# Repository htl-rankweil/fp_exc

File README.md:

# `EXC` - EXtendable Controller (Erweiterbarer Mikrocontroller)

The `EXC` is a microcontroller board with an [ATmega16A](#additional-information)/[ATmega164A](#additional-information). The Board can be powerd over USB or from an external Source (`9-15V`) and used with common Voltages of `3V3` or `5V`. Over the USB port it is also possible to establish a serial (`uart`) connection to a computer. The Board itself offers a `SPI`, `I2C` interface for bus systems, a interface for connection to external interrupts of the microcontroller and a analog interface for reading analog data into the microcontroller. At `DP1` a [Display](#additional-information) can be connected to the board. The available demo firmware offers a quick demonstartion of the board functionallity. Check the [Software](#software) section to get more information.

| Experience | Level |
|:------------|:-----:|
| Soldering   |  |
| Software    |  |

# Downloads

| Type      | File               | Description              |
|:---------:|:------------------:|:-------------------------|
| Schematic | [pdf](https://github.com/0x007E/exc/releases/latest/download/schematic.pdf) / [cadlab](https://cadlab.io/project/28573/main/files) | Schematic files |
| Board | [pdf](https://github.com/0x007E/exc/releases/latest/download/pcb.pdf) / [cadlab](https://cadlab.io/project/28573/main/files) | Board file |
| Drill | [pdf](https://github.com/0x007E/exc/releases/latest/download/drill.pdf) | Drill file |
| Gerber | [zip](https://github.com/0x007E/exc/releases/latest/download/kicad.zip) / [tar](https://github.com/0x007E/exc/releases/latest/download/kicad.tar.gz) | Gerber/Drill files |
| Firmware | [zip](https://github.com/0x007E/exc/releases/latest/download/firmware.zip) / [tar](https://github.com/0x007E/exc/releases/latest/download/firmware.tar.gz) | Firmware for ATmega164A |

# Hardware

The pcb is created with `KiCAD`. All files are built with `github actions` so that they are ready for a production environment.

## PCB

The circuit board is populated on one side. The best way for soldering is within a vapor phase soldering system.

### Top Layer

### Bottom Layer

# Configuration

With Jumper `J13` the `EXC` system is getting bus powered (`5V`). If the system runs with `5V` jumper `J12` has to be shorten between `2-3`. When the system is driven by an external source through the step-down converter the system voltage is switchable between `5V` and `3V3` over the slider switch `SW6`. If `3V3` are choosen the jumper `J12` should be shorten between `1-2`.

> Only change the state of `SW6` with disconnected power source. Also check if jumper `J12` is set correctly!

## LEDs/I2C

To enable the LEDs `LED0-1` jumper `J10` has to be shorten. If the `I2C` interface should be used the jumper `J10` has to be removed.

## UART

The UART of the `ATmega164A` can be coupled with the USB/UART bridge or with the external UART interface at connector `J5`. To set the transmission over USB/UART bridge jumper `J1` and `J2` should be shorten between `1-2`. For the external UART interface jumper `J1` and `J2` should be shorten between `2-3`.

## Display

The display can be powerd constantly over `J99` shorten between `2-3` or controllabe over the microcontroller pin `PA2` and `J99` shorten between `1-2`.

# Programming

The Firmware of the `EXC` can be programmed with [Microchip Studio](#additional-information) over ISP with an [ATMEL ICE](#additional-information) connected to `J9` of the `EXC`. It is necessary to power the board from outside either over USB or the external power supply during programming.

## FUSES

| Register  | Value  |
|:---------:|:------:|
| `HIGH`    | `0xD8` |
| `LOW`     | `0xFF` |

# Software

## Dataflow diagram

## Structogram

# Additional Information

| Type       | Link               | Description              |
|:----------:|:------------------:|:-------------------------|
| Display | [web](https://at.rs-online.com/web/p/lcd-displays-monochrom/5326385) | Display for extendable controller |
| Microchip Studio | [web](https://www.microchip.com/en-us/tools-resources/develop/microchip-studio) | Download Page for Microchip Studio |
| Atmel ICE | [pdf](https://ww1.microchip.com/downloads/en/DeviceDoc/Atmel-ICE_UserGuide.pdf) | Atmel ICE Datasheet |
| ATmega16A | [pdf](https://ww1.microchip.com/downloads/en/devicedoc/atmel-8154-8-bit-avr-atmega16a_datasheet.pdf) | Microchip ATmega16A Datasheet
| ATmega164A | [pdf](https://ww1.microchip.com/downloads/en/devicedoc/atmel-8272-8-bit-avr-microcontroller-atmega164a_pa-324a_pa-644a_pa-1284_p_datasheet.pdf) | Microchip ATmega164A Datasheet |

---

R. GAECHTER

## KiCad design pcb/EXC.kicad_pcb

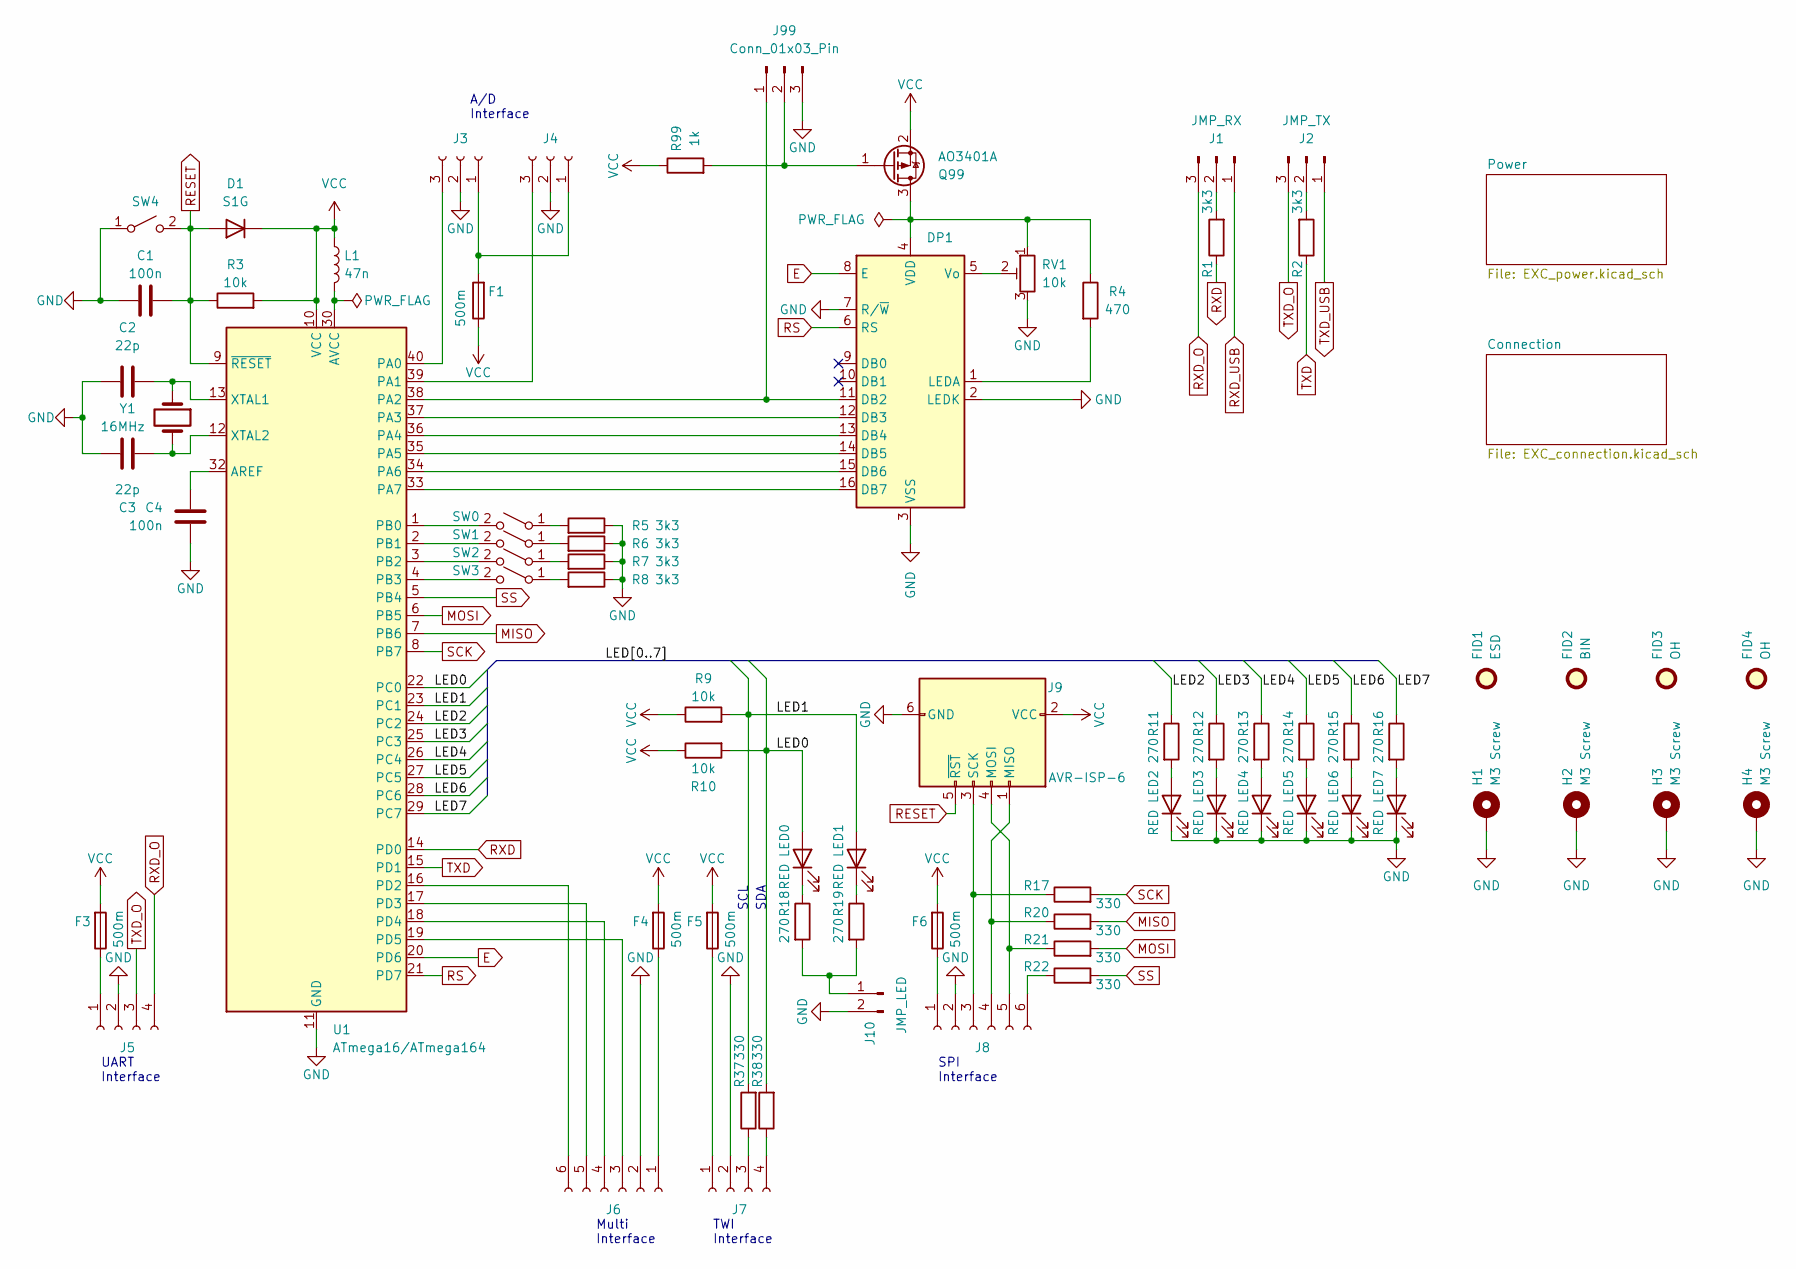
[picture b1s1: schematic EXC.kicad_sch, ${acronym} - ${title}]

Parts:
C1, C4: 100n; C_1206_3216Metric
C2, C3: 22p; C_1206_3216Metric
D1: S1G; D_MiniMELF
DP1: Displaytech_162A_THT
F1, F3, F4, F5, F6: 500m; Fuse_1206_3216Metric
FID1: ESD; ESD-Logo_6.6x6mm_SilkScreen
FID2: BIN; WEEE-Logo_4.2x6mm_SilkScreen
FID3: OH; OSHW-Logo_5.7x6mm_SilkScreen
FID4: OH; QR_0x007e
H1, H2, H3, H4: M3 Screw; MountingHole_3.2mm_M3_DIN965_Pad
J1: JMP_RX; PinHeader_1x03_P2.54mm_Vertical
J2: JMP_TX; PinHeader_1x03_P2.54mm_Vertical
J3, J4: Conn_01x03_Socket; PinSocket_1x03_P2.54mm_Vertical
J5, J7: Conn_01x04_Socket; PinSocket_1x04_P2.54mm_Vertical
J6, J8: Conn_01x06_Socket; PinSocket_1x06_P2.54mm_Vertical
J9: AVR-ISP-6; PinHeader_2x03_P2.54mm_Vertical
J10: JMP_LED; PinHeader_1x02_P2.54mm_Vertical
J99: Conn_01x03_Pin; PinHeader_1x03_P2.54mm_Horizontal
L1: 47n; L_1206_3216Metric_Pad1.42x1.75mm_HandSolder
LED0, LED1, LED2, LED3, LED4, LED5, LED6, LED7: RED; LED_1206_3216Metric
Q99: AO3401A; SOT-23
R1, R2, R5, R6, R7, R8: 3k3; R_1206_3216Metric
R3, R9, R10: 10k; R_1206_3216Metric
R4: 470; R_1206_3216Metric
R11, R12, R13, R14, R15, R16, R18, R19: 270; R_1206_3216Metric
R17, R20, R21, R22, R37, R38: 330; R_1206_3216Metric
R99: 1k; R_1206_3216Metric
RV1: 10k; Potentiometer_Bourns_3266W_Vertical
SW0, SW1, SW2, SW3, SW4: SW_SPST; SW_SPST_PTS645
U1: ATmega16/ATmega164; DIP-40_W15.24mm_LongPads
Y1: 16MHz; Crystal_SMD_Abracon_ABM3-2Pin_5.0x3.2mm

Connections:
/LED0: LED0.2 (A), R10.2, R38.2, U1.22 (PC0)
/LED1: LED1.2 (A), R9.2, R37.2, U1.23 (PC1)
/LED2: R11.1, U1.24 (PC2)
/LED3: R12.1, U1.25 (PC3)
/LED4: R13.1, U1.26 (PC4)
/LED5: R14.1, U1.27 (PC5)
/LED6: R15.1, U1.28 (PC6)
/LED7: R16.1, U1.29 (PC7)
E: DP1.8 (E), U1.20 (PD6)
GND: C1.1, C2.1, C3.1, C4.2, DP1.2 (LEDK), DP1.3 (VSS), DP1.7 (R/~W), H1.1, H2.1, H3.1, H4.1, J3.2, J4.2, J5.2, J6.2, J7.2, J8.2, J9.6 (GND), J10.2, J99.3, LED2.1 (K), LED3.1 (K), LED4.1 (K), LED5.1 (K), LED6.1 (K), LED7.1 (K), R5.1, R6.1, R7.1, R8.1, RV1.3, SW4.1 (A), U1.11 (GND), U1.31 (GND); also elsewhere on the board
MISO: R20.2, U1.7 (PB6)
MOSI: R21.2, U1.6 (PB5)
unnamed: DP1.11 (DB2), J99.1, U1.38 (PA2)
unnamed: DP1.12 (DB3), U1.37 (PA3)
unnamed: DP1.13 (DB4), U1.36 (PA4)
unnamed: DP1.14 (DB5), U1.35 (PA5)
unnamed: DP1.15 (DB6), U1.34 (PA6)
unnamed: DP1.16 (DB7), U1.33 (PA7)
unnamed: DP1.1 (LEDA), R4.2
unnamed: DP1.4 (VDD), Q99.3 (D), R4.1, RV1.1
unnamed: DP1.5 (Vo), RV1.2
unnamed: J1.2, R1.2
unnamed: J2.2, R2.2
unnamed: F1.2, J3.1, J4.1
unnamed: J3.3, U1.40 (PA0)
unnamed: J4.3, U1.39 (PA1)
unnamed: F3.1, J5.1
unnamed: F4.1, J6.1
unnamed: J6.3, U1.19 (PD5)
unnamed: J6.4, U1.18 (PD4)
unnamed: J6.5, U1.17 (PD3)
unnamed: J6.6, U1.16 (PD2)
unnamed: F5.1, J7.1
unnamed: J7.3, R37.1
unnamed: J7.4, R38.1
unnamed: F6.1, J8.1
unnamed: J8.3, J9.3 (SCK), R17.1
unnamed: J8.4, J9.1 (MISO), R20.1
unnamed: J8.5, J9.4 (MOSI), R21.1
unnamed: J8.6, R22.1
unnamed: J10.1, R18.2, R19.2
unnamed: J99.2, Q99.1 (G), R99.2
unnamed: LED0.1 (K), R18.1
unnamed: LED1.1 (K), R19.1
unnamed: LED2.2 (A), R11.2
unnamed: LED3.2 (A), R12.2
unnamed: LED4.2 (A), R13.2
unnamed: LED5.2 (A), R14.2
unnamed: LED6.2 (A), R15.2
unnamed: LED7.2 (A), R16.2
unnamed: R5.2, SW0.1 (A)
unnamed: SW0.2 (B), U1.1 (PB0)
unnamed: R6.2, SW1.1 (A)
unnamed: SW1.2 (B), U1.2 (PB1)
unnamed: R7.2, SW2.1 (A)
unnamed: SW2.2 (B), U1.3 (PB2)
unnamed: R8.2, SW3.1 (A)
unnamed: SW3.2 (B), U1.4 (PB3)
unnamed: C4.1, U1.32 (AREF)
unnamed: L1.2, U1.30 (AVCC)
unnamed: C2.2, U1.13 (XTAL1), Y1.1
unnamed: C3.2, U1.12 (XTAL2), Y1.2
RESET: C1.2, D1.2 (A), J9.5 (~RST), R3.1, SW4.2 (B), U1.9 (~RESET)
RS: DP1.6 (RS), U1.21 (PD7)
RXD: R1.1, U1.14 (PD0)
RXD_O: J1.3, J5.4
RXD_USB: J1.1; also elsewhere on the board
SCK: R17.2, U1.8 (PB7)
SS: R22.2, U1.5 (PB4)
TXD: R2.1, U1.15 (PD1)
TXD_O: J2.3, J5.3
TXD_USB: J2.1; also elsewhere on the board
VCC: D1.1 (K), F1.1, F3.2, F4.2, F5.2, F6.2, J9.2 (VCC), L1.1, Q99.2 (S), R3.2, R9.1, R10.1, R99.1, U1.10 (VCC); also elsewhere on the board

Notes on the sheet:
Multi Interface
UART Interface
A/D Interface
TWI Interface
SCL
SDA
SPI Interface

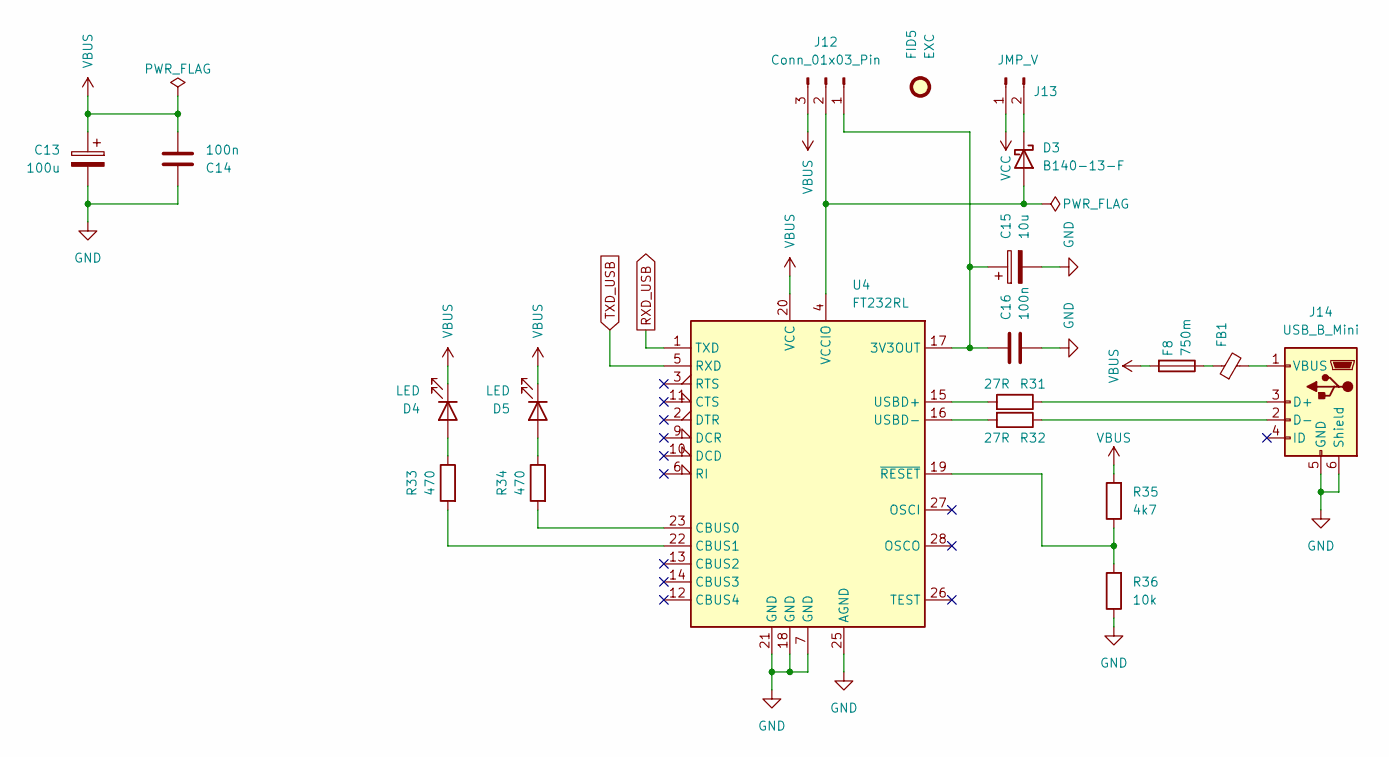
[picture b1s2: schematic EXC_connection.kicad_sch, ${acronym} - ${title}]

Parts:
C13: 100u; CP_Elec_5x5.4
C14, C16: 100n; C_1206_3216Metric
C15: 10u; CP_Elec_5x5.4
D3: B140-13-F; D_SMA
D4, D5: LED; LED_1206_3216Metric
F8: 750m; Fuse_1206_3216Metric
FB1: FerriteBead_Small; L_1206_3216Metric
FID5: EXC; Symbol_Attention_2x2mm_SilkScreen
J12: Conn_01x03_Pin; PinHeader_1x03_P2.54mm_Vertical
J13: JMP_V; PinHeader_1x02_P2.54mm_Vertical
J14: USB_B_Mini; USB_Mini-B_Lumberg_2486_01_Horizontal
R31, R32: 27R; R_1206_3216Metric
R33, R34: 470; R_1206_3216Metric
R35: 4k7; R_1206_3216Metric
R36: 10k; R_1206_3216Metric
U4: FT232RL; SSOP-28_5.3x10.2mm_P0.65mm

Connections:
GND: C13.2, C14.2, C15.2, C16.1, J14.5 (GND), J14.6 (Shield), R36.1, U4.7 (GND), U4.18 (GND), U4.21 (GND), U4.25 (AGND); also elsewhere on the board
unnamed: D3.2 (A), J12.2, U4.4 (VCCIO)
unnamed: D3.1 (K), J13.2
unnamed: D4.2 (A), R33.1
unnamed: D5.2 (A), R34.1
unnamed: F8.1, FB1.1
unnamed: C15.1, C16.2, J12.1, U4.17 (3V3OUT)
unnamed: J14.3 (D+), R31.1
unnamed: J14.2 (D-), R32.1
unnamed: FB1.2, J14.1 (VBUS)
unnamed: R34.2, U4.23 (CBUS0)
unnamed: R33.2, U4.22 (CBUS1)
unnamed: R31.2, U4.15 (USBD+)
unnamed: R32.2, U4.16 (USBD-)
unnamed: R35.1, R36.2, U4.19 (~RESET)
RXD_USB: U4.1 (TXD); also elsewhere on the board
TXD_USB: U4.5 (RXD); also elsewhere on the board
VBUS: C13.1, C14.1, D4.1 (K), D5.1 (K), F8.2, J12.3, R35.2, U4.20 (VCC)
VCC: J13.1; also elsewhere on the board

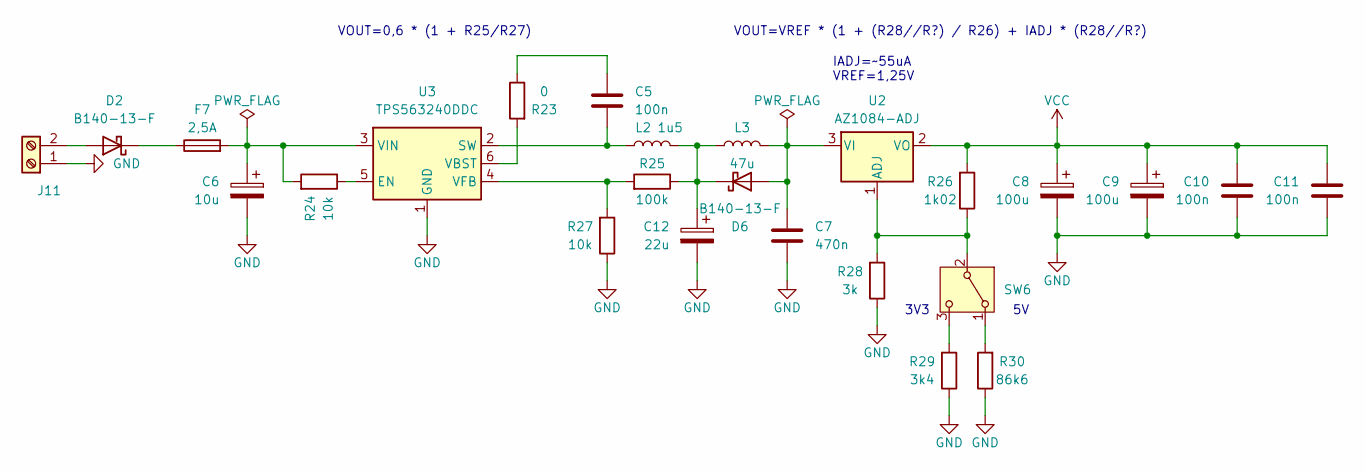
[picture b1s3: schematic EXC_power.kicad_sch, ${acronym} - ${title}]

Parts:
C5, C10, C11: 100n; C_1206_3216Metric
C6: 10u; CP_Elec_5x5.4
C7: 470n; C_1206_3216Metric
C8, C9: 100u; CP_Elec_5x5.4
C12: 22u; CP_Elec_5x5.4
D2, D6: B140-13-F; D_SMA
F7: 2,5A; Fuse_1812_4532Metric
J11: Screw_Terminal_01x02; TerminalBlock_RND_205-00001_1x02_P5.00mm_Horizontal
L2: 1u5; L_Bourns_SRP7028A_7.3x6.6mm
L3: 47u; L_Bourns_SRN8040TA
R23: 0; R_1206_3216Metric
R24, R27: 10k; R_1206_3216Metric
R25: 100k; R_1206_3216Metric
R26: 1k02; R_1206_3216Metric
R28: 3k; R_1206_3216Metric
R29: 3k4; R_1206_3216Metric
R30: 86k6; R_1206_3216Metric
SW6: SW_SPDT; SW_SPDT_CK_JS102011SAQN
U2: AZ1084-ADJ; TO-263-2
U3: TPS563240DDC; SOT-23-6

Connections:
GND: C6.2, C7.1, C8.2, C9.2, C10.1, C11.1, C12.2, J11.1, R27.1, R28.1, R29.1, R30.1, U3.1 (GND); also elsewhere on the board
unnamed: C5.2, R23.1
unnamed: D2.2 (A), J11.2
unnamed: D2.1 (K), F7.1
unnamed: C7.2, D6.2 (A), L3.2, U2.3 (VI)
unnamed: C12.1, D6.1 (K), L2.2, L3.1, R25.1
unnamed: R30.2, SW6.1 (A)
unnamed: R26.1, R28.2, SW6.2 (B), U2.1 (ADJ)
unnamed: R29.2, SW6.3 (C)
unnamed: R24.1, U3.5 (EN)
unnamed: C5.1, L2.1, U3.2 (SW)
unnamed: R23.2, U3.6 (VBST)
unnamed: R25.2, R27.2, U3.4 (VFB)
unnamed: C6.1, F7.2, R24.2, U3.3 (VIN)
VCC: C8.1, C9.1, C10.2, C11.2, R26.2, U2.2 (VO); also elsewhere on the board

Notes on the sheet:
VOUT=0,6 * (1 + R25/R27)
VOUT=VREF * (1 + (R28//R?) / R26) + IADJ * (R28//R?)
3V3
IADJ=~55uA VREF=1,25V

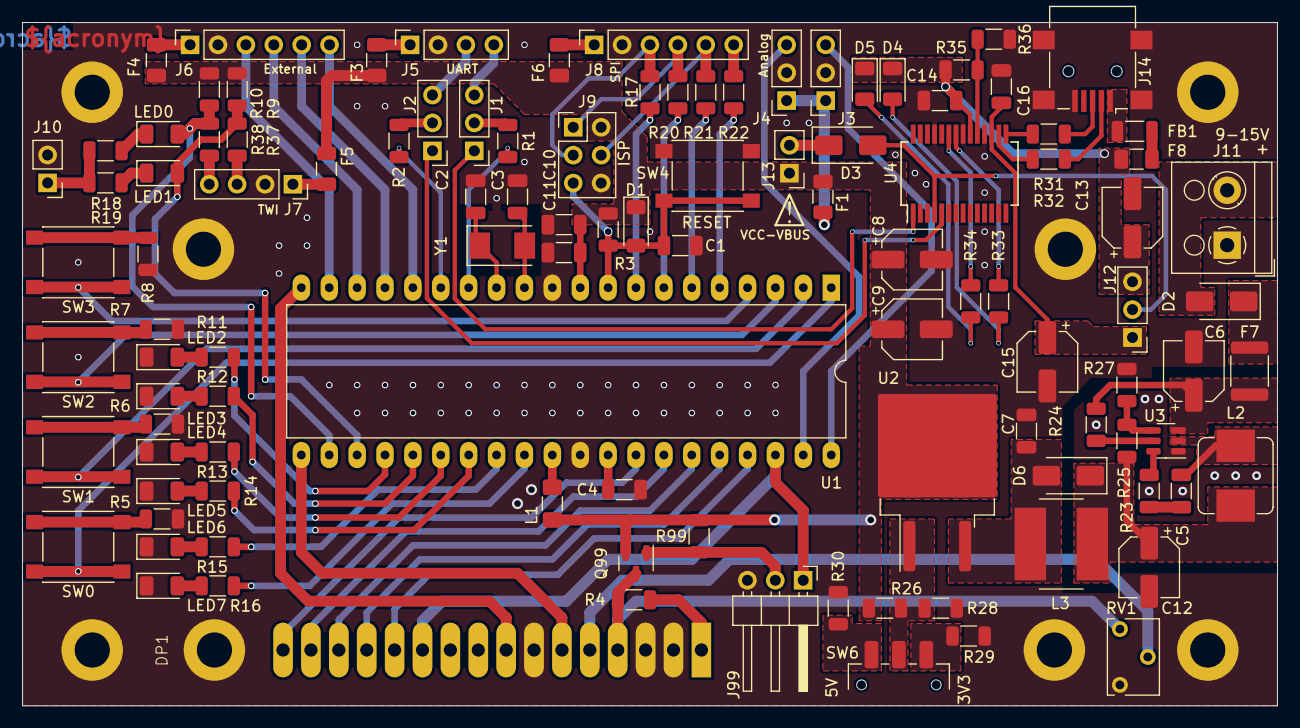
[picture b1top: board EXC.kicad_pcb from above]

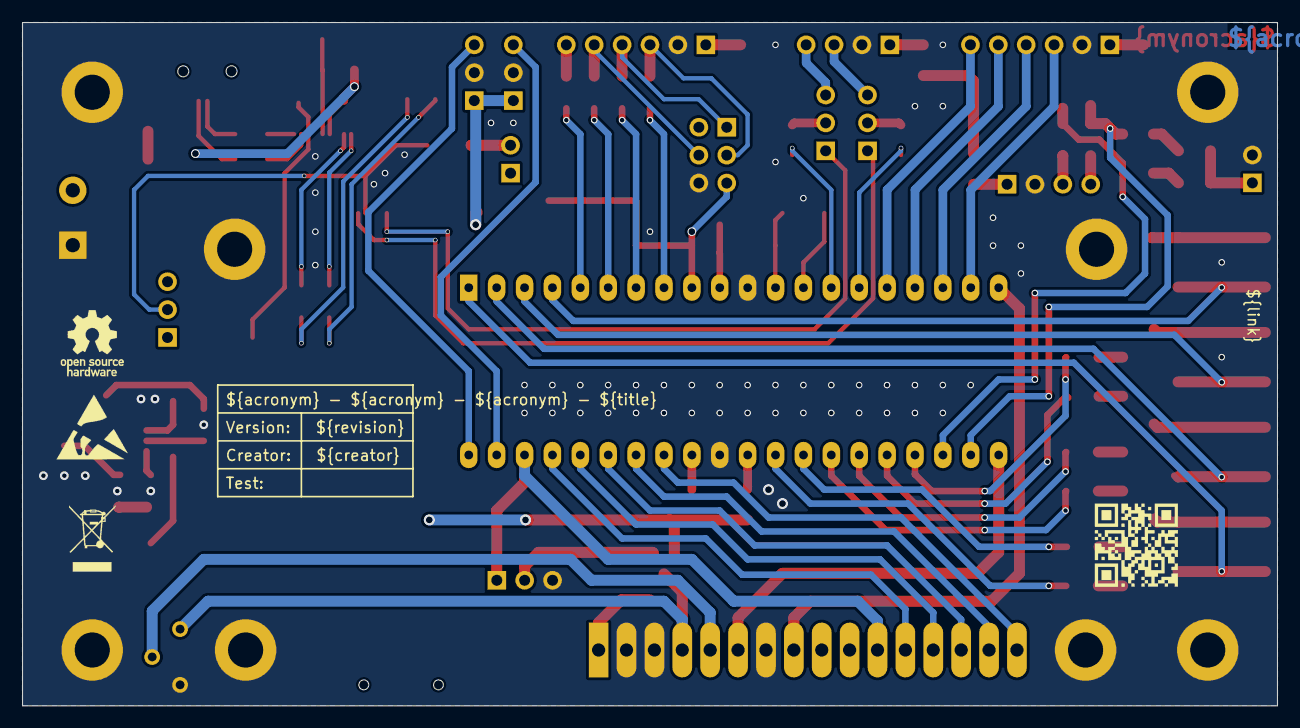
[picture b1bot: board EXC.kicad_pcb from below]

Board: 2 copper layers, 114.3 x 62.2 mm, 118 parts (4 on the bottom side), 101 nets.

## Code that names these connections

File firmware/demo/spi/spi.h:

/* -----------------------------------------
 * G.Raf^engineering
 * www.sunriax.at
 * -----------------------------------------
 *    Platform: Megacard/STK500/STK600
 *    Hardware: ATmega??-????
 * -----------------------------------------
 *     Version: 1.0 Release
 *      Author: G.Raf
 * Description:
 *   Header file for spi library
 * -----------------------------------------
 */

#ifndef SPI_H_
#define SPI_H_

// Definition of SPI parameters

// !!!!!!!!!!!!!!!!!!!!!!!!!!!!!!!!!!!!!
// !!! When device is configured as  !!!
// !!! slave the system clock has to !!!
// !!! be 4 times higher then the    !!!
// !!! SPI clock f_CPU > 4 * f_SPI   !!! 
// !!!!!!!!!!!!!!!!!!!!!!!!!!!!!!!!!!!!! 

#ifndef SPI2X       // Double speed mode
    #define SPI2X
#endif

#ifndef SPI_CLOCK   // SPI_Master shift clock
    // !!!!!!!!!!!!!!!!!!!!!!!!!!!!!!!!!!!!!!!!!!!!!!!!
    // !!! In slave mode the spi clock speed should !!!
    // !!! not exceed f_CPU/4.                      !!!
    // !!!!!!!!!!!!!!!!!!!!!!!!!!!!!!!!!!!!!!!!!!!!!!!!
    //
    // +---------------+-------+------+
    // |         SPI2X |   0   |   1  |
    // +---------------+-------+------+
    // | 0x00 -> F_CPU | / 4   | / 2  |
    // | 0x01 -> F_CPU | / 16  | / 8  |
    // | 0x02 -> F_CPU | / 64  | / 32 |
    // | 0x03 -> F_CPU | / 128 | / 64 |
    // +---------------+-------+------+
    #define SPI_CLOCK 0x03
#endif

#ifndef SPI_DDR     // Port direction register
    #define SPI_DDR DDRB
#endif

#ifndef SPI_PIN     // Pin for SPI setup
    #define SPI_PIN PINB
#endif

#ifndef SPI_PORT    // Port for SPI setup
    #define SPI_PORT PORTB
#endif

#ifndef SPI_SS      // Slave Select
    #define SPI_SS PB4
#endif

#ifndef SPI_MOSI    // Master Out Slave in
    #define SPI_MOSI PB5
#endif

#ifndef SPI_MISO    // Master In Slave Out
    #define SPI_MISO PB6
#endif

#ifndef SPI_SCK     // Clock
    #define SPI_SCK PB7
#endif

//#ifndef SPI_WCOL_PORT // Output for write fault
//      #define SPI_WCOL_PORT PORTB 
//  #ifndef SPI_WCOL_PIN
//      #define SPI_WCOL_PIN PB3
//  #endif
//#endif

// Definition of SPI processing (Enabled = Interrupt/Disabled = Polling)

// !!!!!!!!!!!!!!!!!!!!!!!!!!!!!!!!!!!!!!!!!!!!!!!!!!!
// !!! Interrupts are not included in this library !!!
// !!! If interrupts are used, disable the polling !!!
// !!! by uncommenting the next lines              !!!
// !!!!!!!!!!!!!!!!!!!!!!!!!!!!!!!!!!!!!!!!!!!!!!!!!!!

//#ifndef SPI_SPIE  // SPI Interrupt based processing
//  #define SPI_SPIE
//#endif

#include <avr/io.h>

#ifdef SPI_SPIE
    #include <avr/interrupt.h>
#endif

enum SPI_Mode_t
{
    SPI_Slave=0,
    SPI_Master
};
typedef enum SPI_Mode_t SPI_Mode;

enum SPI_Direction_t
{
    SPI_MSB=0,
    SPI_LSB
};
typedef enum SPI_Direction_t SPI_Direction;

enum SPI_Edge_t
{
    SPI_Rising=0,
    SPI_Falling
};
typedef enum SPI_Edge_t SPI_Polarity;
typedef enum SPI_Edge_t SPI_Phase;

enum SPI_Select_t
{
    SPI_Disable=0,
    SPI_Enable
};
typedef enum SPI_Select_t SPI_Select;

enum SPI_Status_t
{
    SPI_Received=0,
    SPI_Collision,
    SPI_None
};
typedef enum SPI_Status_t SPI_Status;

unsigned char spi_init(SPI_Mode operation, SPI_Direction direction, SPI_Polarity polarity, SPI_Phase phase);
         void spi_disable(void);
         void spi_select(SPI_Select mode);
   SPI_Select spi_slave_select(void);

#ifndef SPI_SPIE
    unsigned char spi_transfer(unsigned char data);
       SPI_Status spi_slave_transfer(unsigned char *data);
#endif

#endif /* SPI_H_ */

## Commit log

2024-10-17 Create pipeline
2024-10-17 Fix wrong path
2024-10-17 Add courtyard overlap filter
2024-10-17 Change switch SW6
2024-10-17 Add display socket
2024-10-17 Change project structure
2024-10-17 Fix build process
2024-10-17 Add README
2024-10-17 Fix cadlab.io link
2024-10-17 Fix firmware name
2024-10-17 Fix wrong filenames
2024-10-17 Fix wrong name
2024-10-18 Add compression
2024-10-18 Revision of README
2024-10-18 Change text position
2024-10-18 Update structogram
2024-10-23 Remove entry
2024-10-23 Change font
2024-10-25 Add fuses

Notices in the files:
README.md:
License CC By-NC-SA
parts and their libraries:
license: CC BY-NC-SA 4.0
